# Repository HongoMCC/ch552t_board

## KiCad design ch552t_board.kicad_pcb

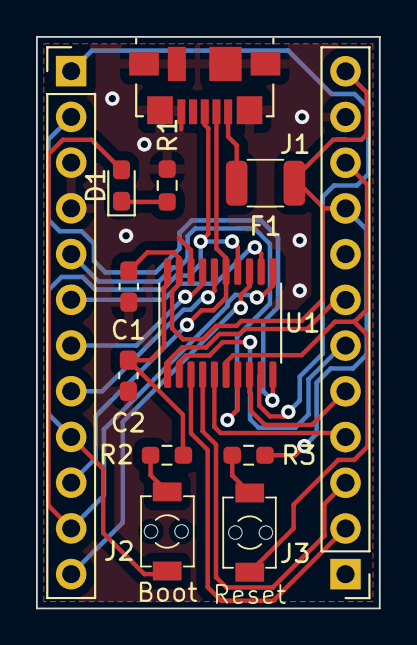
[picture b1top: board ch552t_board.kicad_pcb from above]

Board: 2 copper layers, 19.0 x 31.8 mm, 13 parts (0 on the bottom side), 24 nets.

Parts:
Boot: SW_Push; SW_SPST_TVAF06_A020B_R
C1, C2: C; C_0603_1608Metric_Pad1.08x0.95mm_HandSolder
D1: LED; LED_0603_1608Metric_Pad1.05x0.95mm_HandSolder
F1: Fuse; Fuse_SMD_MF_USMF010
J1: USB_B_Micro; USB_Micro-B_Molex_47346-0001
J2, J3: Conn_01x12_Pin; PinHeader_1x12_P2.54mm_Vertical
R1, R2, R3: R; R_0603_1608Metric_Pad0.98x0.95mm_HandSolder
Reset: SW_Push; SW_SPST_TVAF06_A020B_R
U1: CH552T; TSSOP-20_4.4x6.5mm_P0.65mm

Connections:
/3V3: C2.1, R2.1, U1.20 (3V3)
/P1.0: J2.5, U1.7 (P1.0/T2/CAP1/TIN0)
/P1.1: J3.5, U1.8 (P1.1/T2EX/CAP2/TIN1/VBUS2/AIN0)
/P1.2: J2.7, U1.17 (P1.2/XI/RXD__)
/P1.3: J2.8, U1.16 (P1.3/XO/TXD__)
/P1.4: J3.6, U1.2 (P1.4/T2_/CAP1_/SCS/TIN2/UCC1/AIN1)
/P1.5: J3.2, U1.3 (P1.5/MOSI/PWM1/TIN3/UCC2/AIN2_)
/P1.6: J3.3, U1.4 (P1.6/MISO/RXD1/TIN4_)
/P1.7: J3.4, U1.5 (P1.7/SCK/TXD1/TIN5)
/P3.0: J2.2, U1.10 (P3.0/PWM1_/RXD)
/P3.1: J2.1, U1.9 (P3.1/PWM2_/TXD_)
/P3.2: J3.7, U1.1 (P3.2/TXD1_/INT0/VBUS1/AIN3)
/P3.3: D1.2 (A), J2.11, U1.11 (P3.3/INT1)
/P3.4: J2.6, U1.12 (P3.4/PWM2/RXD1_/T0)
/P3.5: J2.12, U1.13 (P3.5/T1)
/P3.6: Boot.1, J1.3 (D+), J2.9, U1.14 (P3.6/UDP)
/P3.7: J1.2 (D-), J2.10, U1.15 (P3.7/UDM)
/reset: J3.10, Reset.2, U1.6 (RST/T2EX_/CAP2__)
GND: C1.2, C2.2, J1.5 (GND), J1.6 (Shield), J2.3, J2.4, J3.11, R1.2, U1.18 (GND/VSS)
unnamed: D1.1 (K), R1.1
unnamed: F1.1, J1.1 (VBUS)
unnamed: Boot.2, R2.2
unnamed: R3.2, Reset.1
VCC: C1.1, F1.2, J3.9, J3.12, R3.1, U1.19 (VCC/VDD)
